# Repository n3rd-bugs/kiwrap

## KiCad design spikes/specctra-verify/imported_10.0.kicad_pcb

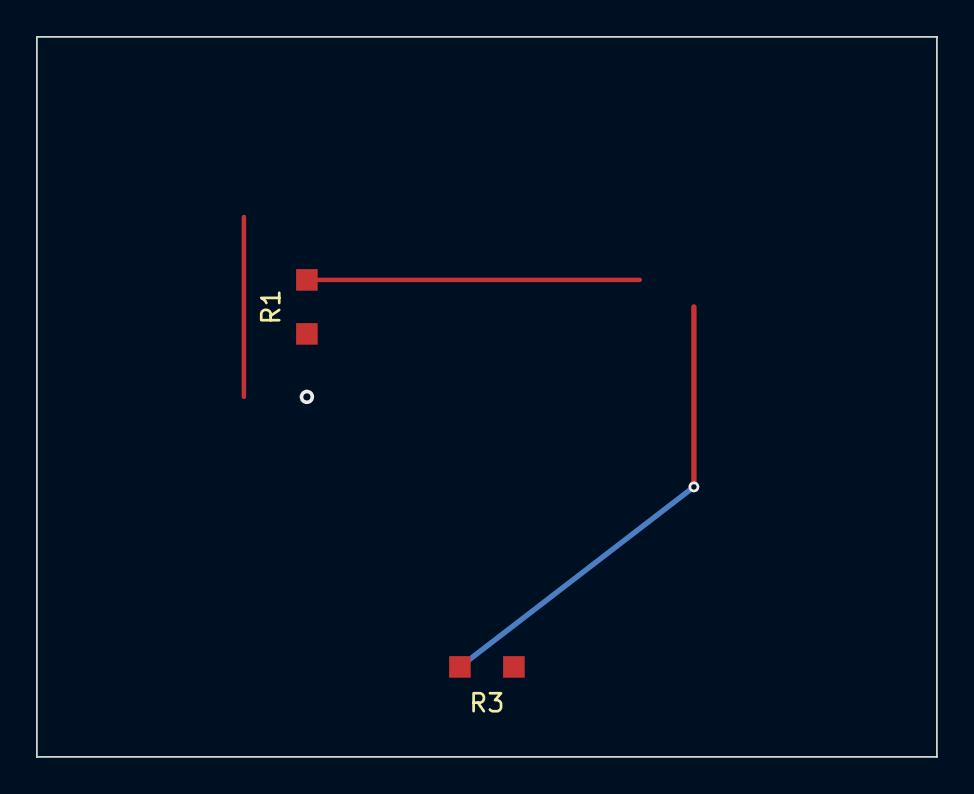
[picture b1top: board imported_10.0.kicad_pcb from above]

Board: 2 copper layers, 50.0 x 40.0 mm, 3 parts (1 on the bottom side), 3 nets.

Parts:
R1, R2, R3: 10k; R2

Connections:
NET1: R1.1, R2.1
NET2: R1.2, R3.1
NET3: R2.2, R3.2
